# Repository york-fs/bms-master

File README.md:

# Battery Management System Master Board

The BMS master board which connects to a daisy chain of distributed segment boards and continuously checks all
critical values. Two linear hall effect current sensors are sampled to measure the main DC battery current.

## Features

* **I2C Communication to Distributed Segment Boards**
* **Dual-Pole Current Sensing**
  * Uses open-loop hall effect current sensors
* **CAN Communication**
* **Active-High Open-Drain Shutdown Output**
  * Driven high to ~10.9 volts to indicate healthy state
  * High impedance in a fault state
  * Matches the Bender ISOMETER IR155-3204 IMD
* **eFuse and TVS Protected LVS Input**
  * Designed for 12 volt nominal input
  * Overvoltage lockout at ~16.7 volts
* **Microcontroller Watchdog with 3V3 Rail Monitoring**
* **EEPROM Config**

## Cloning

A recursive clone must be used to download the `kicad-library` repository:

    git clone --recursive https://github.com/york-fs/bms-master.git

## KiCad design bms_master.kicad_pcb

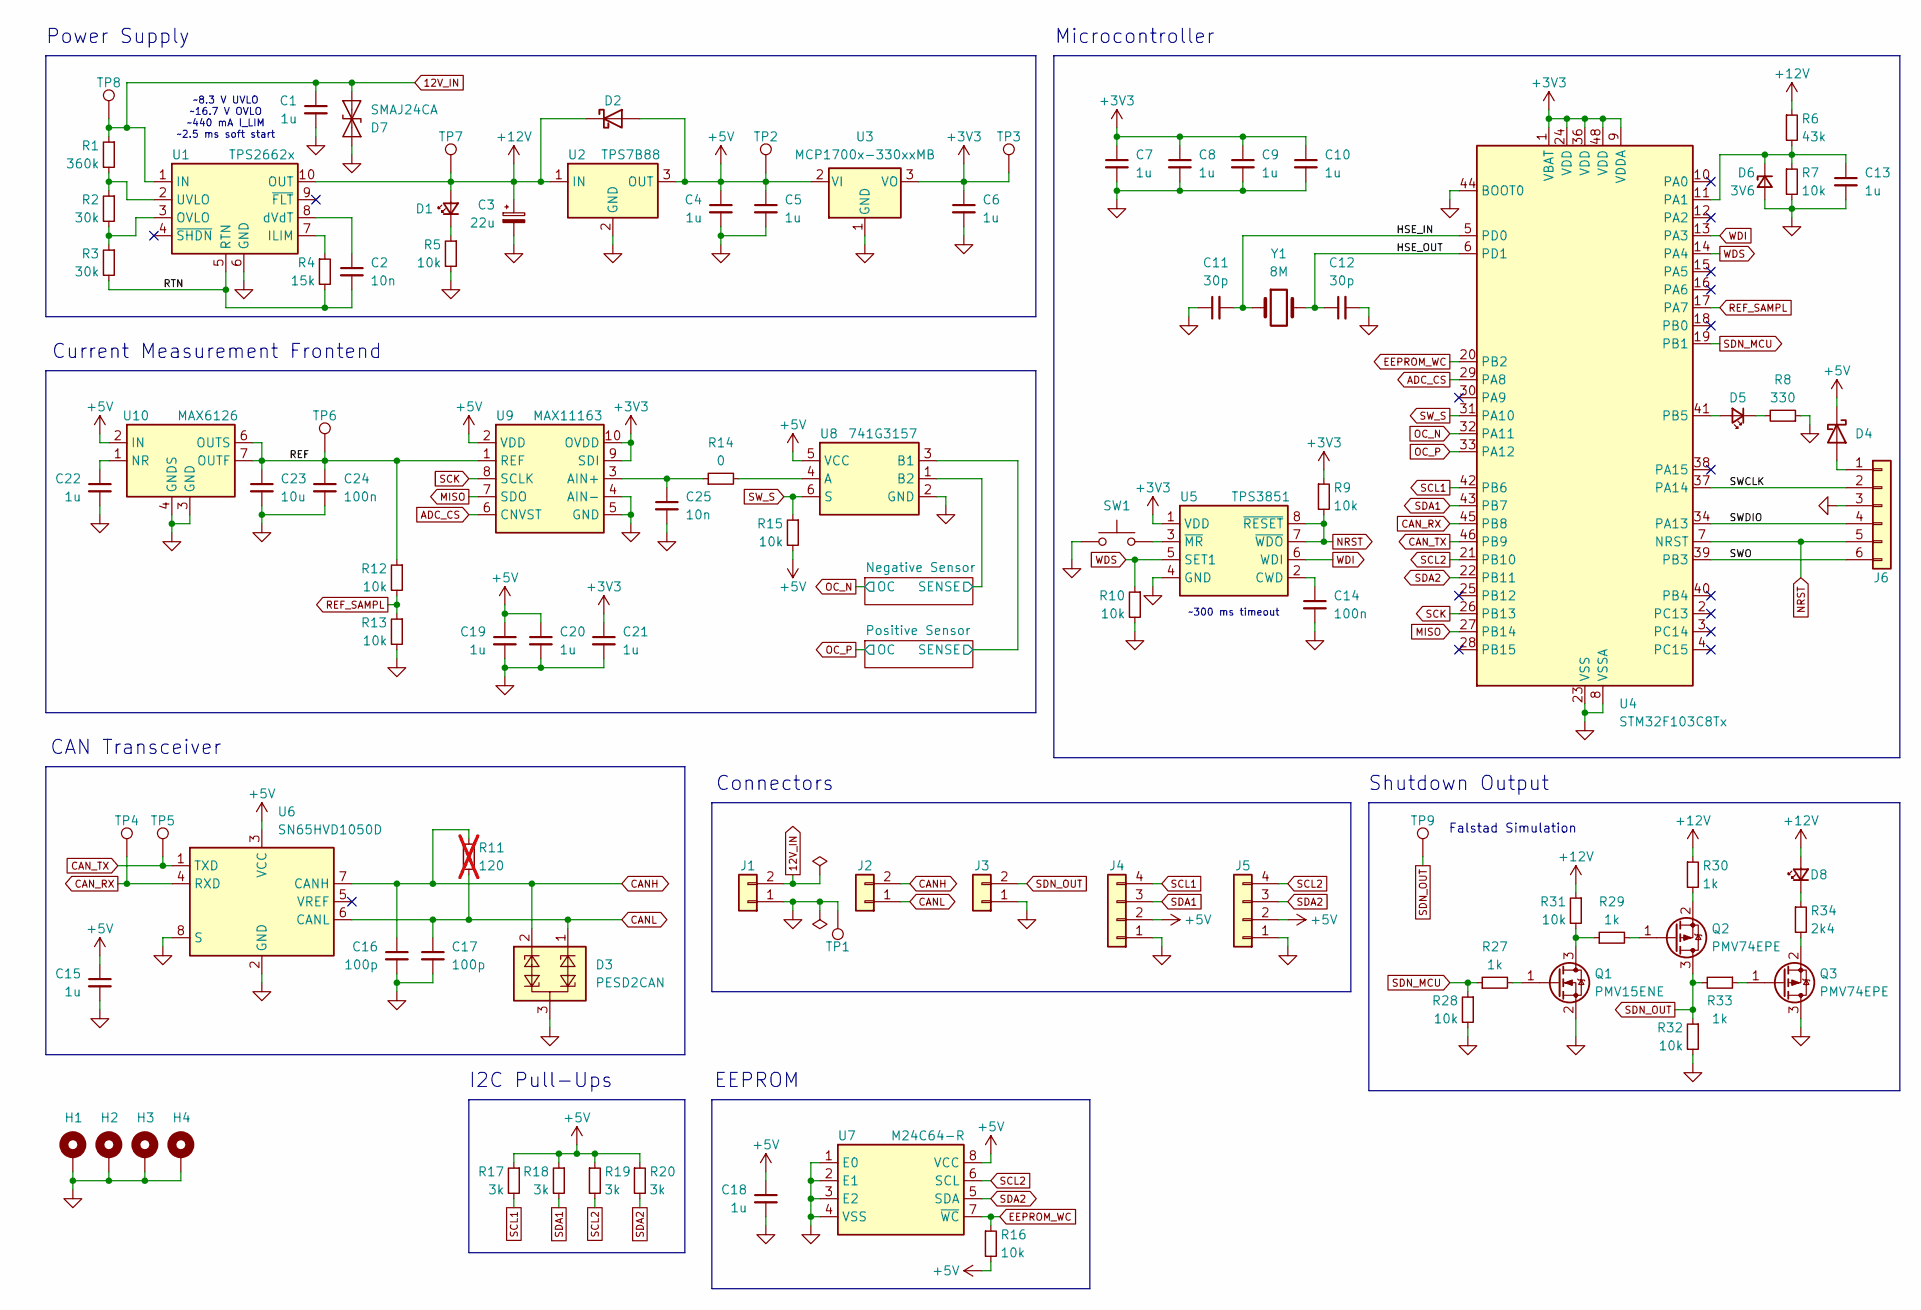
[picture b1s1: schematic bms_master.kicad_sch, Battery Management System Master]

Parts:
C1, C4, C5, C6, C7, C8, C9, C10, C13, C15, C18, C19, C20, C21, C22: 1u; C_0603_1608Metric; Mfr # CL10B105KB8NQNC
C2, C25: 10n; C_0603_1608Metric; Mfr # GRM1885C1H103JA01D
C3: 22u; CP_Elec_6.3x7.7; Mfr # EEEFK1J220XP
C11, C12: 30p; C_0603_1608Metric; Mfr # GQM1875C2E300GB12D
C14, C24: 100n; C_0603_1608Metric; Mfr # CL10B104KB8NNNC
C16, C17: 100p; C_0603_1608Metric; Mfr # GCM1885C2A101JA16D
C23: 10u; C_1206_3216Metric; Mfr # GRM31CR71C106KA12L
D1, D5, D8: LED_Small; LED_0603_1608Metric; Mfr # NCD0603R1
D2, D4: D_Schottky; D_SOD-323; Mfr # NSR0530H
D3: PESD2CAN; SOT-23; Mfr # PESD2CAN,215
D6: 3V6; D_SOD-323; Mfr # BZX384C3V6
D7: SMAJ24CA; D_SMA; Mfr # SMAJ24CA
H1, H2, H3, H4: MountingHole_Pad; MountingHole_3.2mm_M3_Pad_Via
J1: Conn_01x02; MolexMicrofitPlus1x2; Mfr # 2157601022
J2: Conn_01x02; MolexMicrofitPlus1x2; Mfr # 2157601012
J3: Conn_01x02; MolexMicrofitPlus1x2; Mfr # 2157601032
J4, J5: Conn_01x04; MolexMicrofitPlus1x4; Mfr # 2157601004
J6: Conn_01x06; IDC-Connector-2x3; Mfr # HX JN1.27-2x3P ZZ H4.9
Q1: PMV15ENE; SOT-23; Mfr # PMV15ENER
Q2, Q3: PMV74EPE; SOT-23; Mfr # PMV74EPER
R1: 360k; R_0603_1608Metric
R2, R3: 30k; R_0603_1608Metric
R4: 15k; R_0603_1608Metric
R5, R7, R9, R10, R12, R13, R15, R16, R28, R31, R32: 10k; R_0603_1608Metric; Mfr # 0603WAF1002T5E
R6: 43k; R_0603_1608Metric
R8: 330; R_0603_1608Metric; Mfr # 0603WAF3300T5E
R11: 120; R_0603_1608Metric; not fitted
R14: 0; R_0603_1608Metric; Mfr # 0603WAF0000T5E
R17, R18, R19, R20: 3k; R_0603_1608Metric; Mfr # 0603WAF3001T5E
R27, R29, R30, R33: 1k; R_0603_1608Metric; Mfr # 0603WAF1001T5E
R34: 2k4; R_0603_1608Metric
SW1: SW_Push; SW_Push_1P1T_NO_Vertical_Wuerth_434133025816; Mfr # SKRPACE010
TP1, TP2, TP3, TP4, TP5, TP6, TP7, TP8, TP9: TestPoint; TestPoint_Keystone_5000-5004_Miniature
U1: TPS2662x; VSON-10-1EP_3x3mm_P0.5mm_EP1.65x2.4mm; Mfr # TPS26625
U2: TPS7B88; TO-252-2; Mfr # TPS7B8850QKVURQ1
U3: MCP1700x-330xxMB; SOT-89-3; Mfr # MCP1700T-3302E/MB
U4: STM32F103C8Tx; LQFP-48_7x7mm_P0.5mm; Mfr # STM32F103C8T6
U5: TPS3851; VSON-8-1EP_3x3mm_P0.65mm_EP1.6x2.4mm; Mfr # TPS3851G33S
U6: SN65HVD1050D; SOIC-8_3.9x4.9mm_P1.27mm; Mfr # SN65HVD1050DR
U7: M24C64-R; SOIC-8_3.9x4.9mm_P1.27mm; Mfr # M24C64-RMN6TP
U8: 741G3157; SOT-363_SC-70-6; Mfr # SN74LVC1G3157DCKR
U9: MAX11163; MSOP-10_3x3mm_P0.5mm; Mfr # MAX11163EUB+
U10: MAX6126; SOIC-8_3.9x4.9mm_P1.27mm; Mfr # MAX6126BASA41+
Y1: 8M; Crystal_SMD_5032-2Pin_5.0x3.2mm; Mfr # X50328MSB2GI

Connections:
12V_IN: C1.1, D7.2 (A2), J1.2, R1.1, TP8.1, U1.1 (IN)
+3V3: C6.1, C7.1, C8.1, C9.1, C10.1, C21.1, R9.1, TP3.1, U3.3 (VO), U4.1 (VBAT), U4.9 (VDDA), U4.24 (VDD), U4.36 (VDD), U4.48 (VDD), U5.1 (VDD), U9.9 (SDI), U9.10 (OVDD); also elsewhere on the board
+5V: C4.1, C5.1, C15.1, C18.1, C19.1, C20.1, D2.2 (A), D4.1 (K), J4.2, J5.2, R15.2, R16.2, R17.1, R18.1, R19.1, R20.1, TP2.1, U2.3 (OUT), U3.2 (VI), U6.3 (VCC), U7.8 (VCC), U8.5 (VCC), U9.2 (VDD), U10.2 (IN); also elsewhere on the board
+12V: C3.1, D1.2 (A), D2.1 (K), D8.2 (A), R6.1, R30.1, R31.1, TP7.1, U1.10 (OUT), U2.1 (IN)
/HSE_IN: C11.2, U4.5 (PD0), Y1.1
/HSE_OUT: C12.1, U4.6 (PD1), Y1.2
/Negative Sensor/SENSE: U8.1 (B2); also elsewhere on the board
/Positive Sensor/SENSE: U8.3 (B1); also elsewhere on the board
/REF: C23.1, C24.1, R12.1, TP6.1, U9.1 (REF), U10.6 (OUTS), U10.7 (OUTF)
/RTN: C2.2, R3.2, R4.2, U1.5 (RTN), U1.11 (RTN)
/SWCLK: J6.2, U4.37 (PA14)
/SWDIO: J6.4, U4.34 (PA13)
/SWO: J6.6, U4.39 (PB3)
ADC_CS: U4.29 (PA8), U9.6 (CNVST)
CANH: C16.1, D3.2 (C2), J2.2, R11.1, U6.7 (CANH)
CANL: C17.1, D3.1 (C1), J2.1, R11.2, U6.6 (CANL)
CAN_RX: TP4.1, U4.45 (PB8), U6.4 (RXD)
CAN_TX: TP5.1, U4.46 (PB9), U6.1 (TXD)
EEPROM_WC: R16.1, U4.20 (PB2), U7.7 (~WC)
GND: C1.2, C3.2, C4.2, C5.2, C6.2, C7.2, C8.2, C9.2, C10.2, C11.1, C12.2, C13.2, C14.2, C15.2, C16.2, C17.2, C18.2, C19.2, C20.2, C21.2, C22.2, C23.2, C24.2, C25.2, D3.3 (CC), D6.2 (A), D7.1 (A1), H1.1, H2.1, H3.1, H4.1, J1.1, J3.1, J4.1, J5.1, J6.3, Q1.2 (S), Q3.3 (D), R5.2, R7.2, R8.1, R10.2, R13.2, R28.2, R32.2, SW1.1, TP1.1, U1.6 (GND), U2.2 (GND), U3.1 (GND), U4.8 (VSSA), U4.23 (VSS), U4.35 (VSS), U4.44 (BOOT0), U4.47 (VSS), U5.4 (GND), U5.9 (GND), U6.2 (GND), U6.8 (S), U7.1 (E0), U7.2 (E1), U7.3 (E2), U7.4 (VSS), U8.2 (GND), U9.4 (AIN-), U9.5 (GND), U10.3 (GND), U10.4 (GNDS); also elsewhere on the board
MISO: U4.27 (PB14), U9.7 (SDO)
NRST: J6.5, R9.2, U4.7 (NRST), U5.7 (~WDO), U5.8 (~RESET)
unnamed: D1.1 (K), R5.1
unnamed: D4.2 (A), J6.1
unnamed: D5.2 (A), U4.41 (PB5)
unnamed: D5.1 (K), R8.2
unnamed: C13.1, D6.1 (K), R6.2, R7.1, U4.11 (PA1)
unnamed: D8.1 (K), R34.1
unnamed: Q1.3 (D), R29.1, R31.2
unnamed: Q1.1 (G), R27.2
unnamed: Q2.1 (G), R29.2
unnamed: Q2.2 (S), R30.2
unnamed: Q3.1 (G), R33.1
unnamed: Q3.2 (S), R34.2
unnamed: R4.1, U1.7 (ILIM)
unnamed: R2.2, R3.1, U1.3 (OVLO)
unnamed: R1.2, R2.1, U1.2 (UVLO)
unnamed: C2.1, U1.8 (dVdT)
unnamed: C14.1, U5.2 (CWD)
unnamed: SW1.2, U5.3 (~MR)
unnamed: R14.2, U8.4 (A)
unnamed: C25.1, R14.1, U9.3 (AIN+)
unnamed: C22.1, U10.1 (NR)
OC_N: U4.32 (PA11); also elsewhere on the board
OC_P: U4.33 (PA12); also elsewhere on the board
REF_SAMPL: R12.2, R13.1, U4.17 (PA7)
SCK: U4.26 (PB13), U9.8 (SCLK)
SCL1: J4.4, R17.2, U4.42 (PB6)
SCL2: J5.4, R19.2, U4.21 (PB10), U7.6 (SCL)
SDA1: J4.3, R18.2, U4.43 (PB7)
SDA2: J5.3, R20.2, U4.22 (PB11), U7.5 (SDA)
SDN_MCU: R27.1, R28.1, U4.19 (PB1)
SDN_OUT: J3.2, Q2.3 (D), R32.1, R33.2, TP9.1
SW_S: R15.1, U4.31 (PA10), U8.6 (S)
WDI: U4.13 (PA3), U5.6 (WDI)
WDS: R10.1, U4.14 (PA4), U5.5 (SET1)

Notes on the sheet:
Power Supply
I2C Pull-Ups
~8.3 V UVLO ~16.7 V OVLO ~440 mA I_LIM ~2.5 ms soft start
Falstad Simulation
Microcontroller
Connectors
~300 ms timeout
EEPROM
Shutdown Output
CAN Transceiver
Current Measurement Frontend

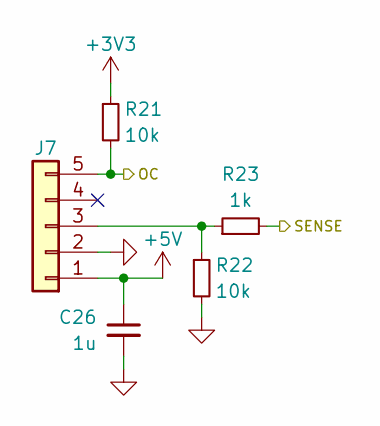
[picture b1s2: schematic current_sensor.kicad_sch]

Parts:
C26: 1u; C_0603_1608Metric; Mfr # CL10B105KB8NQNC
J7: Conn_01x05; JST_PH_S5B-PH-K_1x05_P2.00mm_Horizontal; Mfr # S5B-PH-K-S(LF)(SN)
R21, R22: 10k; R_0603_1608Metric; Mfr # 0603WAF1002T5E
R23: 1k; R_0603_1608Metric; Mfr # 0603WAF1001T5E

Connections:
+3V3: R21.1; also elsewhere on the board
+5V: C26.1, J7.1; also elsewhere on the board
/Positive Sensor/SENSE: R23.2; also elsewhere on the board
GND: C26.2, J7.2, R22.2; also elsewhere on the board
unnamed: J7.3, R22.1, R23.1
OC_P: J7.5, R21.2; also elsewhere on the board

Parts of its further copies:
C27: 1u; C_0603_1608Metric; Mfr # CL10B105KB8NQNC
J8: Conn_01x05; JST_PH_S5B-PH-K_1x05_P2.00mm_Horizontal; Mfr # S5B-PH-K-S(LF)(SN)
R24, R25: 10k; R_0603_1608Metric; Mfr # 0603WAF1002T5E
R26: 1k; R_0603_1608Metric; Mfr # 0603WAF1001T5E

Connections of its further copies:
+3V3: R24.1; also elsewhere on the board
+5V: C27.1, J8.1; also elsewhere on the board
/Negative Sensor/SENSE: R26.2; also elsewhere on the board
GND: C27.2, J8.2, R25.2; also elsewhere on the board
unnamed: J8.3, R25.1, R26.1
OC_N: J8.5, R24.2; also elsewhere on the board

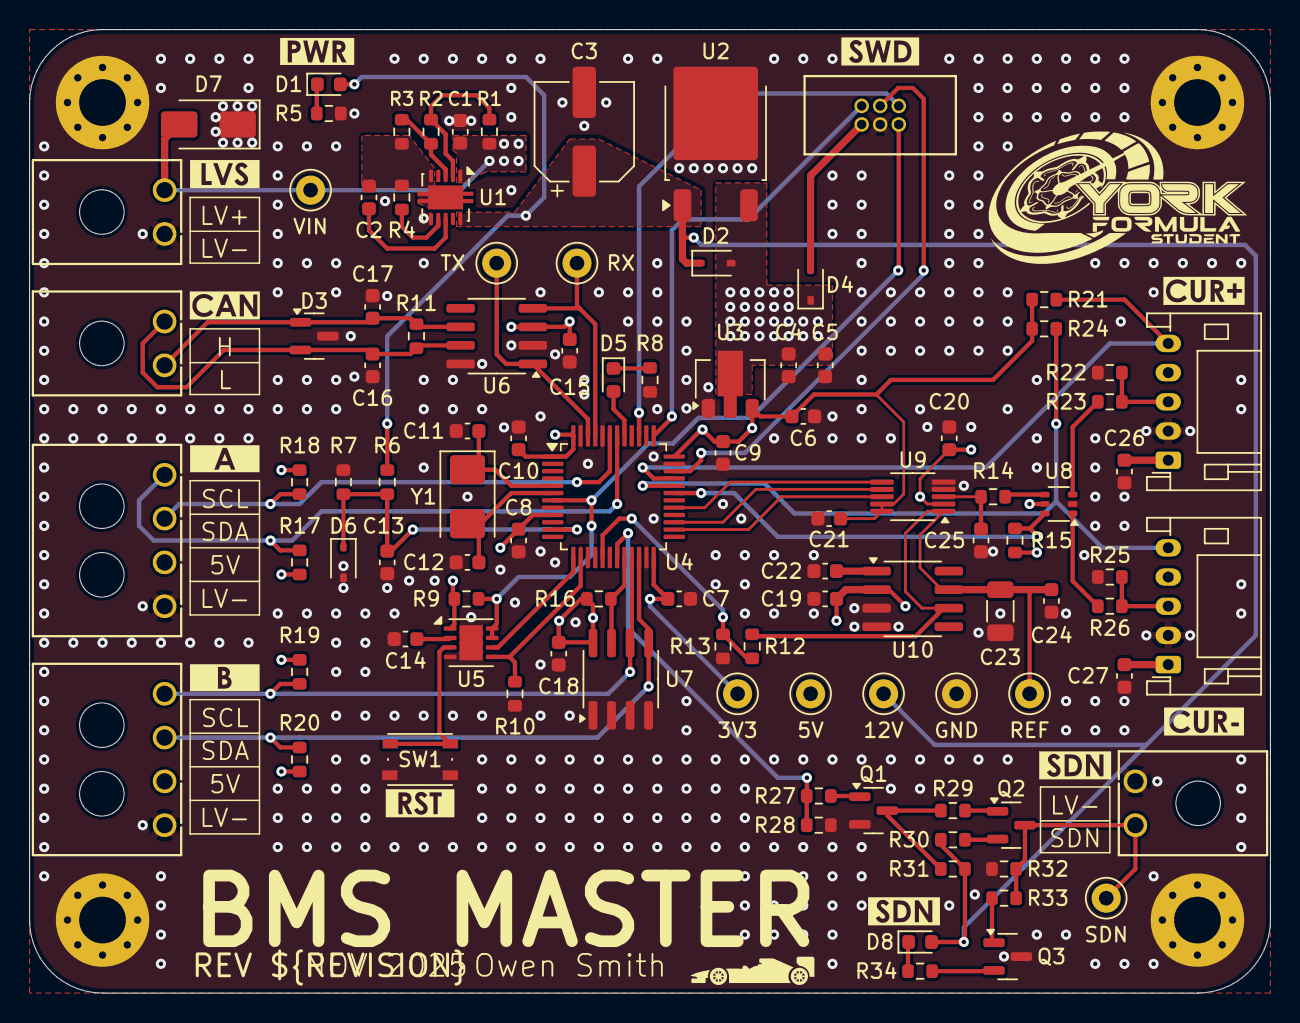
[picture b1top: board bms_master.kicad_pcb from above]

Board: 4 copper layers, 85.0 x 66.0 mm, 116 parts (0 on the bottom side), 58 nets.

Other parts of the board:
kibuzzard-6910B7D7: G***; kibuzzard-6910B7D7
kibuzzard-6910B9F6, kibuzzard-6910B9F6#2: G***; kibuzzard-6910B9F6
kibuzzard-6910B84D: G***; kibuzzard-6910B84D
kibuzzard-6910B743: G***; kibuzzard-6910B743
kibuzzard-6910B859: G***; kibuzzard-6910B859
kibuzzard-6910BA7C: G***; kibuzzard-6910BA7C
kibuzzard-6910BA67: G***; kibuzzard-6910BA67
kibuzzard-6910BB6B: G***; kibuzzard-6910BB6B
kibuzzard-6910BB45: G***; kibuzzard-6910BB45
kibuzzard-6910BB76: G***; kibuzzard-6910BB76

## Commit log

2025-04-27 schematic: Add shutdown and charge enable outputs
2025-04-27 schematic: Measure 12V rail with STM ADC
2025-04-27 schematic: Re-annotate designators
2025-04-27 schematic: Fix overcurrent pin pull-up voltage
2025-04-27 schematic: Assign some net classes
2025-05-04 schematic: Assign most footprints
2025-05-04 schematic: Fill in most BOM info
2025-05-04 schematic: Allow powering 5V rail from SWD header
2025-05-04 schematic: Choose a footprint for the main connector
2025-05-04 pcb: Setup PCB settings
2025-05-04 *: Add initial PCB layout
2025-05-04 pcb: Move connectors slightly towards board edge
2025-05-04 pcb: Add some more silkscreen
2025-05-05 pcb: Improve silkscreen and add a few more GND vias
2025-05-05 *: Bump issue date
2025-05-05 pcb: Run cleanup graphics
2025-05-05 pcb: Run cleanup tracks
2025-05-05 pcb: Move OC_N track slightly
2025-05-11 pcb: Add some more GND vias
2025-05-11 pcb: Add GND between SPI lines
2025-05-11 pcb: Set gerber output parameters
2025-06-04 *: Update library references and move SWD header slightly
2025-06-07 *: Change all 100k pull-up and pull-downs to 10k
2025-06-07 pcb: Remove unnecessary 5V via for test point
2025-06-07 *: Add a test point for the reference
2025-06-18 *: Mirror I2C connector pin order
2025-06-18 pcb: Update even more library references
2025-06-18 pcb: Remove some 5V vias
2025-06-18 pcb: Enable PTH thermal reliefs for 5V and GND planes
2025-06-18 pcb: Improve silkscreen
2025-06-18 *: Bump to revision B
2025-10-05 meta: Add kicad-library submodule
2025-10-05 pcb: Update to new kicad libraries
2025-10-05 schematic: Switch to new symbol library
2025-10-05 meta: Update gitignore
2025-10-05 meta: Add README
2025-10-05 meta: Fix gitmodules formatting
2025-10-05 ci: Add workflow which installs KiCad
2025-10-05 meta: Update kicad-library submodule
2025-10-05 ci: Run ERC and DRC checks
2025-10-05 ci: Generate and upload kicad artifacts
2025-10-05 ci: Generate drill files
2025-10-05 ci: Upload a separate gerbers artifact
2025-10-05 ci: Upload stats and image to pages
2025-10-05 meta: Add some badges and a render to the README
2025-10-09 ci: Use reusable workflow from monorepo
2025-10-19 meta: Add .lck files to gitignore
2025-10-19 *: Use GND via mounting holes
2025-10-20 *: Rework current measurement frontend
    * Add decoupling to sensor VCC
    * Lower filter capacitor value from 1u to 10n
    * Add series resistors from sensor outputs
    * Add pull-downs on sensor outputs
2025-10-23 project: Add footprint library
2025-10-24 kicad-library: Update to latest version
2025-10-25 *: Switch to Molex Micro-Fit+ for main connectors
    * Switch to Micro-Fit+ for power, CAN, I2C and shutdown
    * Change the I2C connector pin order
    * Switch to smaller Schottky diodes
    * Resize the board to 85 mm x 65 mm
    * Remove the charge enable output as it's currently not needed
2025-10-26 bom: Remove Sim.Pins and Sim.Device
2025-10-26 schematic: Move connectors to a block
2025-10-26 *: Switch to new SWD header and reset button
2025-10-27 *: Add 12V shutdown output circuit
2025-10-27 *: Add 12V test point
2025-11-04 *: Use an eFuse on the 12 LVS input
2025-11-04 pcb: Update some connector footprint references
2025-11-05 *: Use more suitable MOSFETs in the shutdown circuit
2025-11-07 *: Change shutdown MOSFET gate resistors to 1k
    This provides more protection and reduces BOM count.
2025-11-07 *: Add a current limiting resistor to the shutdown output
    This reduces the output level to around 10.9 volts.
2025-11-08 *: Connect the reference to an STM ADC pin
    Also change the EEPROM_WC pin.
2025-11-08 *: Update 12 volt rail measurement circuit
    Select a zener and increase the upper resistor slightly.
2025-11-08 *: Add TPS3851 watchdog IC
2025-11-09 pcb: Update Molex 1x4 connectors from library
2025-11-09 pcb: Cleanup connector silkscreen
2025-11-09 *: Reorder reference designators
2025-11-09 pcb: Cleanup vias and designator silkscreen
2025-11-09 pcb: Cleanup some empty islands
2025-11-09 pcb: Make board edge round
    Also indent mounting holes to 5 mm instead of 4 mm.
2025-11-09 pcb: Move shutdown LED down slightly
2025-11-09 pcb: Move 3V3 test point
2025-11-09 pcb: Add GND via for ADC
2025-11-09 *: Add shutdown test point
2025-11-10 pcb: Add a couple more GND vias
2025-11-10 *: Switch from the TPS25961 eFuse to the TPS26625
2025-11-10 *: Add a TVS diode on the LVS input
2025-11-10 *: Bump revision and dates
2025-11-10 pcb: Run track cleanup
2025-11-10 schematic: Add link to simulation of shutdown output
2025-11-11 bom: Cleanup BOM
2025-11-11 meta: Update README
2025-11-22 meta: Set LF line endings explicitly
2025-11-23 ci: Update to latest kicad workflow
2025-11-23 meta: Add more badges to the README
2026-01-31 schematic: Fix WDI pin direction shape
